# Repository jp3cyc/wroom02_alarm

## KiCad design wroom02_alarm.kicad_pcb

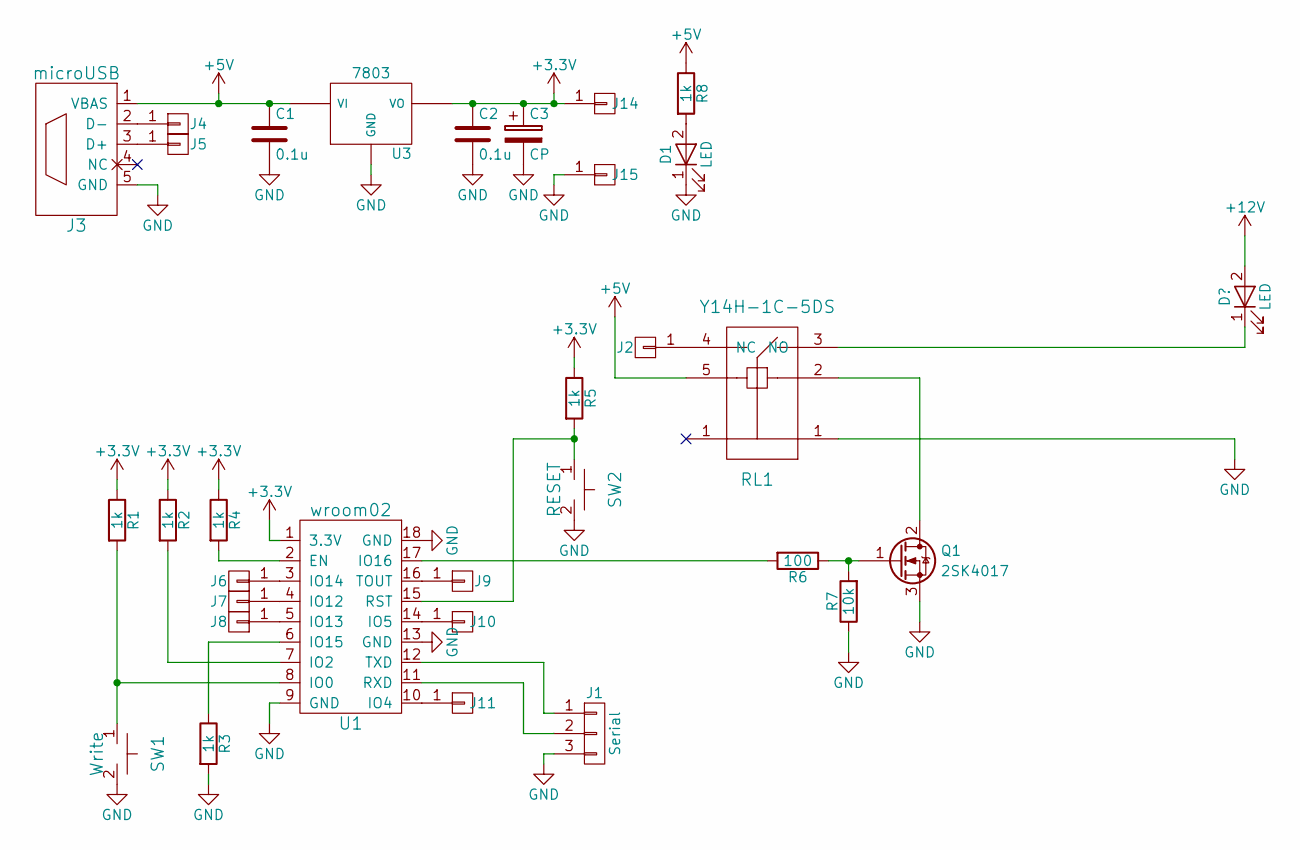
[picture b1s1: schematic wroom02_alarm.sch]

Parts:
C1, C2: 0.1u; C_0603_HandSoldering
C3: CP; CP_Radial_D8.0mm_P2.50mm
D1: LED; LED_0603_HandSoldering
J1: Serial; Pin_Header_Straight_1x03_Pitch2.54mm
J2, J4, J5, J6, J7, J8, J9, J10, J11, J14, J15: pin; universal
J3: microUSB
Q1: 2SK4017; TO-220_Vertical
R1, R2, R3, R4, R5, R8: 1k; R_0603_HandSoldering
R6: 100; R_0603_HandSoldering
R7: 10k; R_0603_HandSoldering
RL1: Y14H-1C-5DS
SW1: Write; switch
SW2: RESET; switch
U1: wroom02; WROOM02
U3: 7803; TO-252-3_TabPin2

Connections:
+3V3: C2.1, C3.1, J14.1, R1.1, R2.1, R4.1, R5.1, U1.1 (3.3V), U3.VO
+5V: C1.1, J3.1 (VBAS), R8.1, RL1.5, U3.VI
unnamed: D1.2 (A), R8.2
unnamed: J1.1, U1.12 (TXD)
unnamed: J1.2, U1.11 (RXD)
unnamed: J2.1, RL1.4 (NC)
unnamed: J3.2 (D-), J4.1
unnamed: J3.3 (D+), J5.1
unnamed: J6.1, U1.3 (IO14)
unnamed: J7.1, U1.4 (IO12)
unnamed: J8.1, U1.5 (IO13)
unnamed: J9.1, U1.16 (TOUT)
unnamed: J10.1, U1.14 (IO5)
unnamed: J11.1, U1.10 (IO4)
unnamed 14: RL1.3 (NO); also elsewhere on the board
unnamed: Q1.1 (G), R6.1, R7.2
unnamed: Q1.2 (D), RL1.2
unnamed: R1.2, SW1.1, U1.8 (IO0)
unnamed: R2.2, U1.7 (IO2)
unnamed: R3.1, U1.6 (IO15)
unnamed: R4.2, U1.2 (EN)
unnamed: R5.2, SW2.1, U1.15 (RST)
unnamed: R6.2, U1.17 (IO16)

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
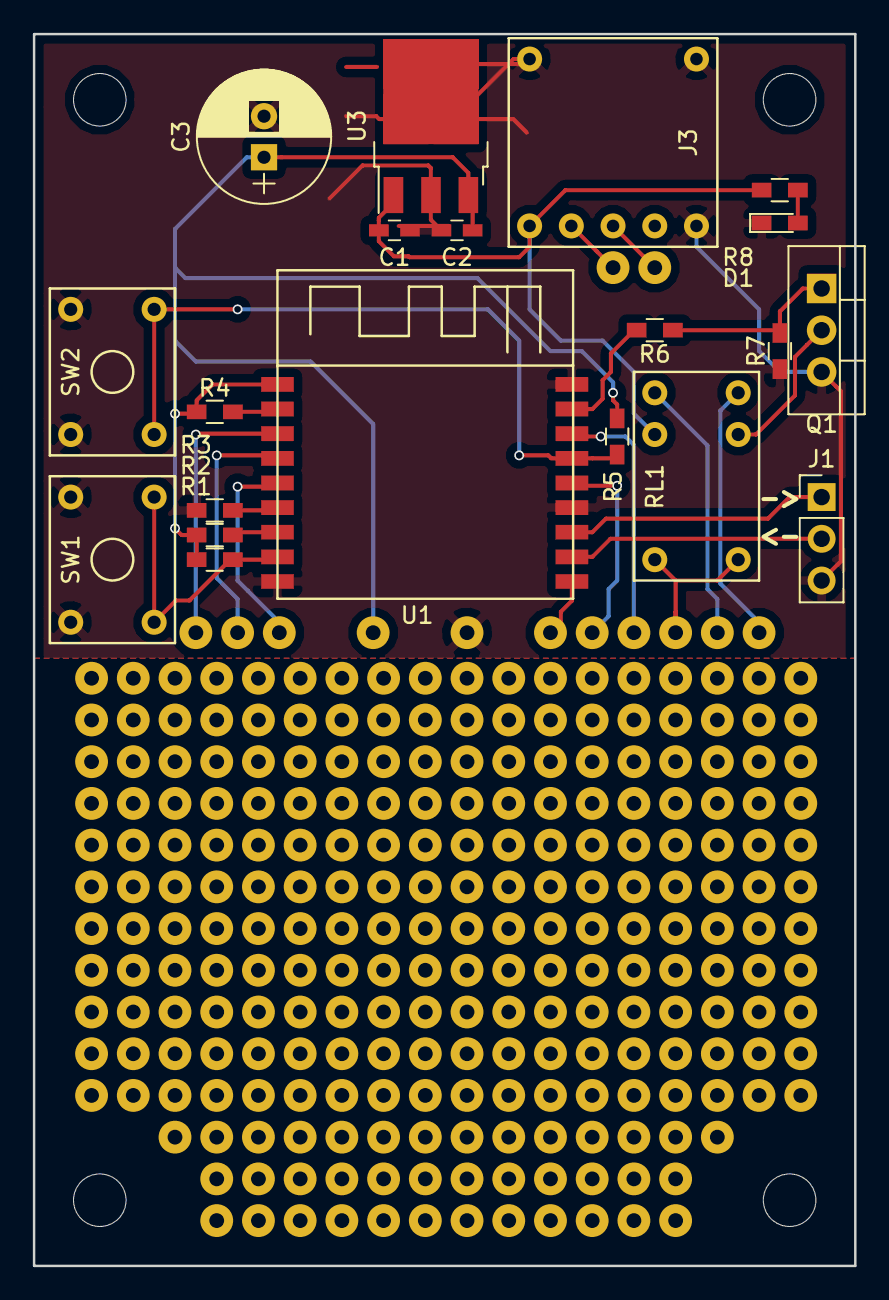
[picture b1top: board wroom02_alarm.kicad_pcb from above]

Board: 2 copper layers, 50.0 x 75.0 mm, 33 parts (0 on the bottom side), 25 nets.

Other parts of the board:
J12, J13: pin; universal

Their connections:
unnamed 14: J12.1; also elsewhere on the board

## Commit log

2017-07-24 基本回路
2017-07-24 DRCエラーを修正
2017-07-24 基板も完成
2017-07-24 製造ファイル作成
2017-07-24 pcbファイルも一緒に圧縮していたので削除
2017-07-24 100x100に拡張
2017-07-26 基板サイズを変更
    Fusionにドリルが多すぎるって怒られた．
2017-09-24 GBRを作成
2017-10-27 akicartのURLを追加
